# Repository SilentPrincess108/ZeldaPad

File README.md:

# ZeldaPad
A custom zelda-themed macropad made for Hack Club's Stasis!! I created this project as a start on the path to make my ow keyboard1 This taught me some of the basics of matrix wiring, creating the pcb for keyboards, as well as QMK software to set them up!

# BOM
|Name              |Purpose                         |Quantity|Total Cost (USD)|Link                                                                                                                                                                                                                                                                                                                                                                                                                                                                                                                                                                                                                                                                                                                                                                           |Distributor|
|------------------|--------------------------------|--------|----------------|-------------------------------------------------------------------------------------------------------------------------------------------------------------------------------------------------------------------------------------------------------------------------------------------------------------------------------------------------------------------------------------------------------------------------------------------------------------------------------------------------------------------------------------------------------------------------------------------------------------------------------------------------------------------------------------------------------------------------------------------------------------------------------|-----------|
|PCB               |Board to connect all components.|5       |5.80            |https://jlcpcb.com/                                                                                                                                                                                                                                                                                                                                                                                                                                                                                                                                                                                                                                                                                                                                                            |JLCPCB     |
|XIAO RP 2040      |Board for firmware              |1       |3.59            |https://www.aliexpress.com/item/1005003908237026.html?spm=a2g0o.cart.0.0.6df938dabXCDew&mp=1&pdp_npi=6%40dis%21CAD%21CAD%2011.73%21CAD%204.93%21%21CAD%204.75%21%21%21%40210328df17740487064442830e3672%2112000056511616306%21ct%21CA%217451194651%21%216%210%21                                                                                                                                                                                                                                                                                                                                                                                                                                                                                                               |Aliexpress |
|Cherry MX Switches|Switches for keys               |10      |2.60            |https://www.aliexpress.com/item/1005008811335051.html?spm=a2g0o.cart.0.0.6df938dabXCDew&mp=1&pdp_npi=6%40dis%21CAD%21CAD%2052.73%21CAD%2045.79%21%21CAD%2044.15%21%21%21%40210328df17740487064442830e3672%2112000046764301536%21ct%21CA%217451194651%21%211%210%21                                                                                                                                                                                                                                                                                                                                                                                                                                                                                                             |Aliexpress |
|Rotary Encoders   |Volume control on my macropad   | 10     | 14.45          |https://www.amazon.ca/DIYhz-Degree-Encoder-Digital-Potentiometer/dp/B07D3D64X7/ref=sr_1_19?adgrpid=1363396993354142&dib=eyJ2IjoiMSJ9.cLzMV8QJine-uRY42fwe54NLnvfmRupJ_xVbn--YGR9v84XhSecKITLZBCeGS7DFrFOYC6xY7WYlo86Vf7aPcQJvqH6wbSELKvNqjvSgf4H_3efpMWXRmQos6GTDiGnOkFxtYZIAzkTZSGgOzPn7D-AYrDMabkqtD1K0MZg1Q7MPypl1c7vCEvs2H-bxf4aAsPyJaTyW88M95eAkF3VHiCygaoBzEgyfRsLOxfJl6BZTAW922Nj758S2U2CK_YLV5k76pgvZNVKA_aEU_BS-SMxtcnF-wgCRhjiNvDPk5Yc.skms3t_QGYLNxxUjoFg2SYQTCFqsNlsPW_WlpExInAo&dib_tag=se&hvadid=85212721065801&hvbmt=be&hvdev=c&hvlocphy=124370&hvnetw=o&hvqmt=e&hvtargid=kwd-85213510155146%3Aloc-32&hydadcr=3373_13608418&keywords=rotary+encoder+amazon&mcid=f5d8e45f1de33b8d98341eb9916be8fb&msclkid=53019b4e734f1aa2ec62f2b72f5754a3&qid=1777949754&sr=8-19|Amazon     |

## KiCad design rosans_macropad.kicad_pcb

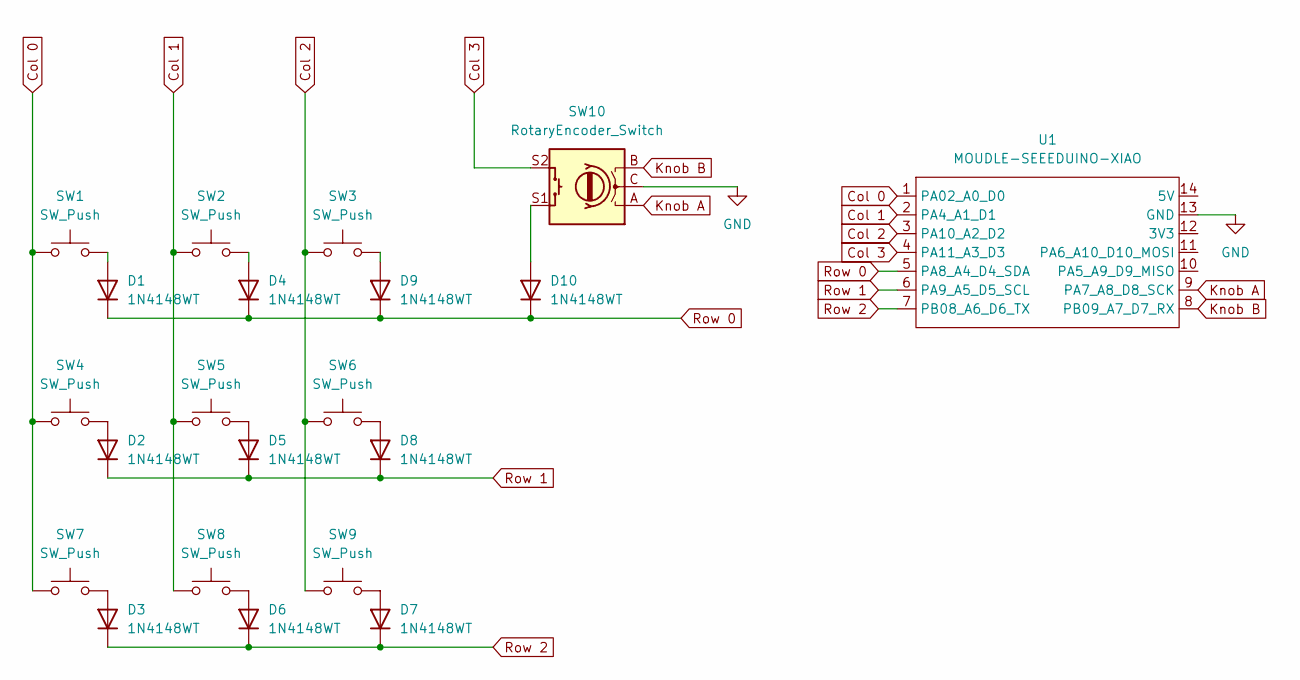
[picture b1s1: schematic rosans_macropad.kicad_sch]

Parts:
D1, D2, D3, D4, D5, D6, D7, D8, D9, D10: 1N4148WT; D_SOD-523
SW1, SW2, SW3, SW4, SW5, SW6, SW7, SW8, SW9: SW_Push; SW_Cherry_MX_1.00u_PCB
SW10: RotaryEncoder_Switch; RotaryEncoder_Alps_EC11E-Switch_Vertical_H20mm
U1: MOUDLE-SEEEDUINO-XIAO; XIAO-Generic-Hybrid-14P-2.54-21X17.8MM

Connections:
Col 0: SW1.1, SW4.1, SW7.1, U1.1 (PA02_A0_D0)
Col 1: SW2.1, SW5.1, SW8.1, U1.2 (PA4_A1_D1)
Col 2: SW3.1, SW6.1, SW9.1, U1.3 (PA10_A2_D2)
Col 3: SW10.S2, U1.4 (PA11_A3_D3)
GND: SW10.C, U1.13 (GND)
Knob A: SW10.A, U1.9 (PA7_A8_D8_SCK)
Knob B: SW10.B, U1.8 (PB09_A7_D7_RX)
unnamed: D1.2 (A), SW1.2
unnamed: D2.2 (A), SW4.2
unnamed: D3.2 (A), SW7.2
unnamed: D4.2 (A), SW2.2
unnamed: D5.2 (A), SW5.2
unnamed: D6.2 (A), SW8.2
unnamed: D7.2 (A), SW9.2
unnamed: D8.2 (A), SW6.2
unnamed: D9.2 (A), SW3.2
unnamed: D10.2 (A), SW10.S1
Row 0: D1.1 (K), D4.1 (K), D9.1 (K), D10.1 (K), U1.5 (PA8_A4_D4_SDA)
Row 1: D2.1 (K), D5.1 (K), D8.1 (K), U1.6 (PA9_A5_D5_SCL)
Row 2: D3.1 (K), D6.1 (K), D7.1 (K), U1.7 (PB08_A6_D6_TX)

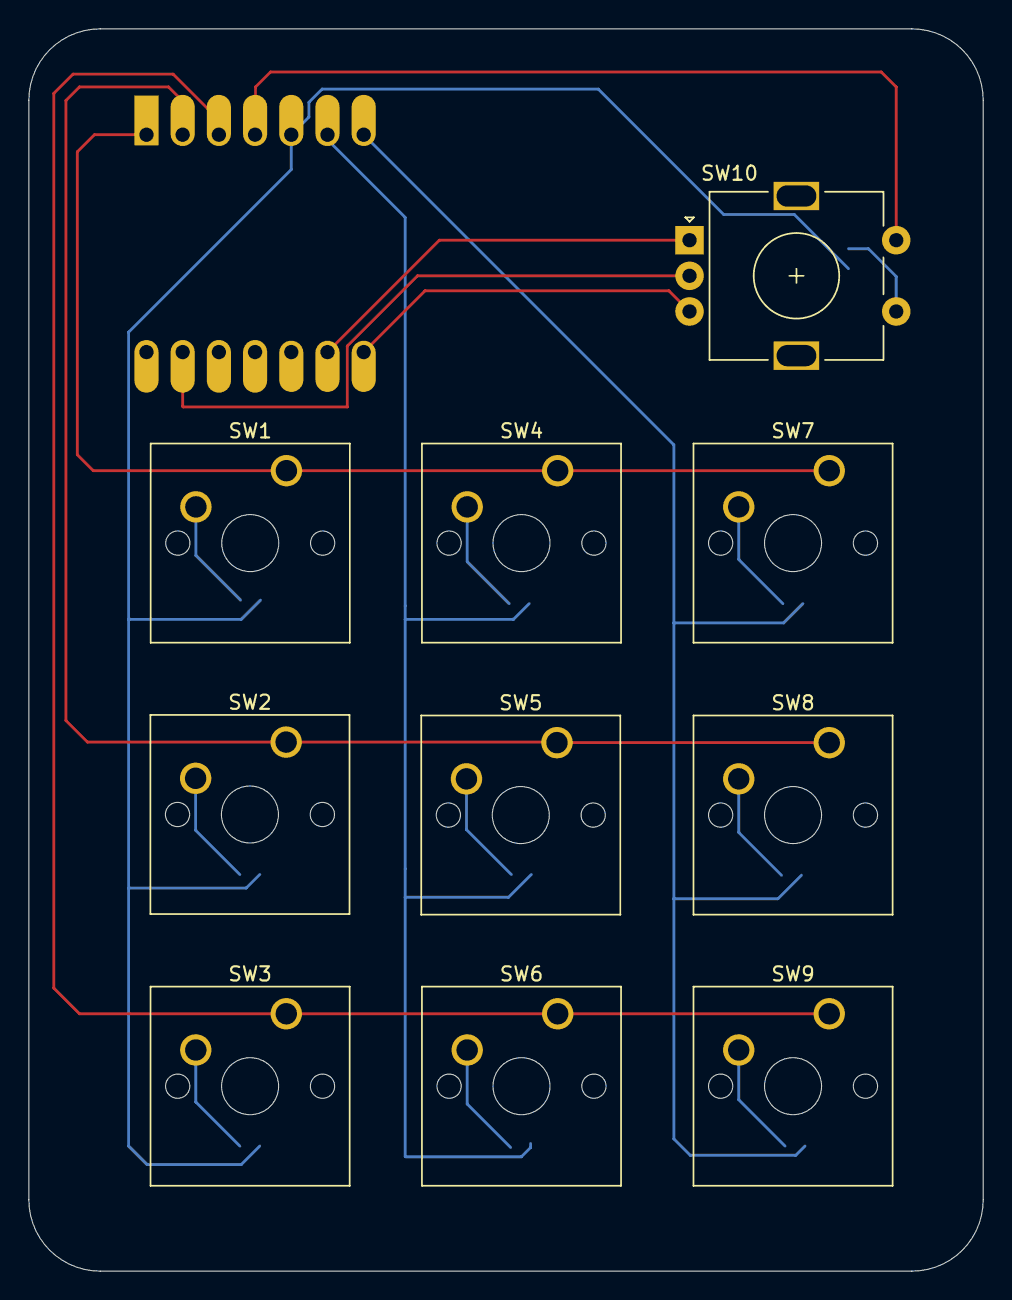
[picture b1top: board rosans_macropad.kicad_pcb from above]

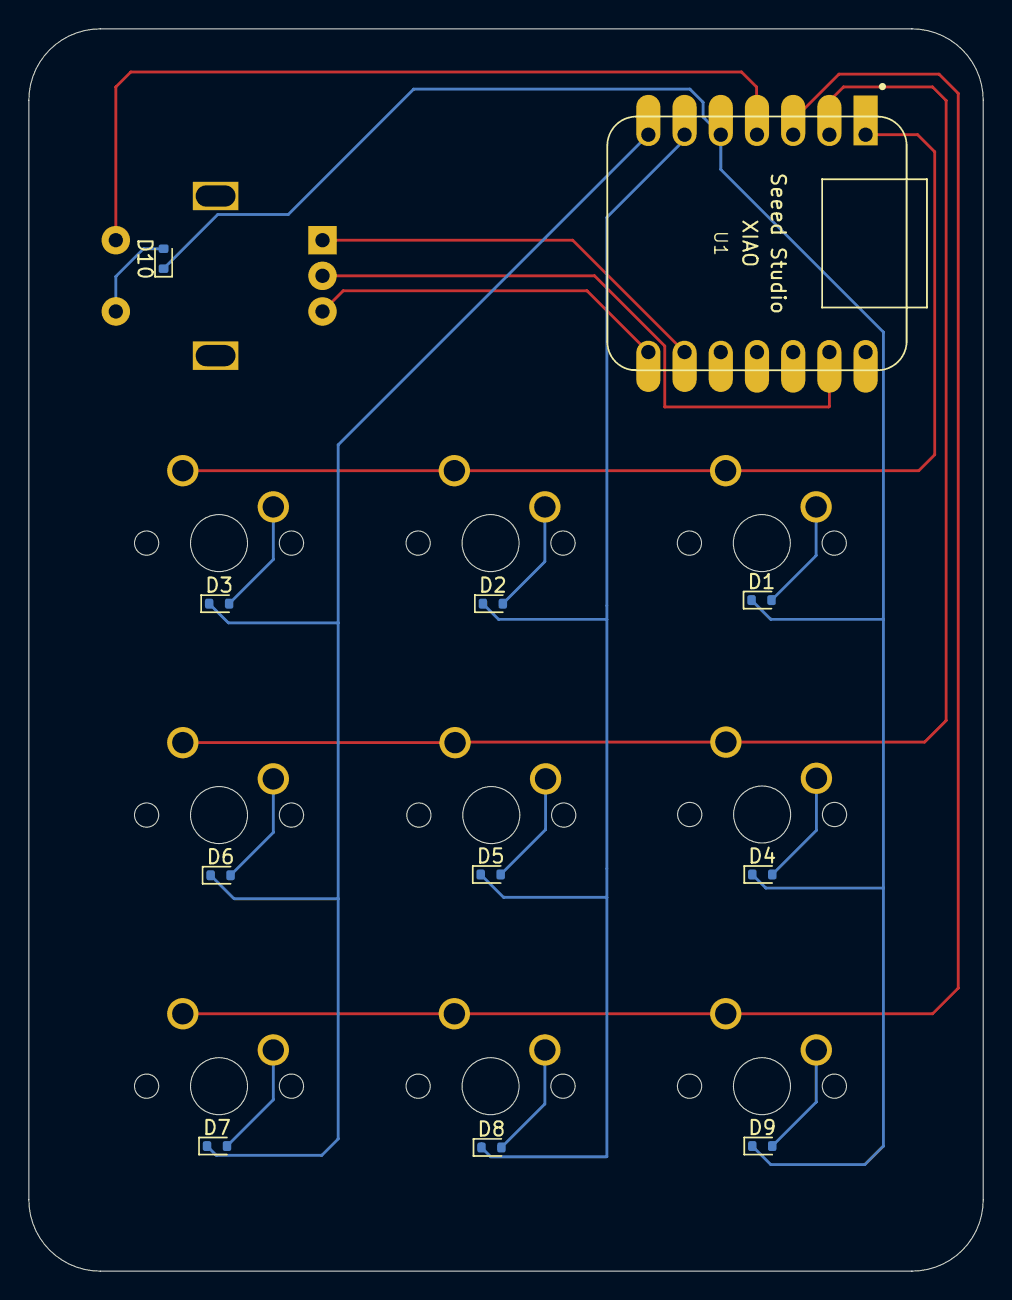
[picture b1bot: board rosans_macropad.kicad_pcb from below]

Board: 2 copper layers, 66.9 x 87.2 mm, 21 parts (11 on the bottom side), 20 nets.

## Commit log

2026-05-04 Update README with project details and BOM
    Expanded project description and added BOM table with components.
2026-05-04 added firmware
2026-05-05 added updated bom
2026-05-05 Update BOM section with additional components
